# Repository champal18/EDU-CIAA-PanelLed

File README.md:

# EDU-CIAA-PanelLed
Poncho EDU-CIAA

Proyecto de alumnos de ingenieria en computacion de la Universidad Nacional de La Plata.
Desarrollo de poncho para EDU-CIA NXP.
Controlador de panel led + Interfaz de usuario.

Firmware y diseño completo. Se adjunta el informe final para facilitar su comprension.

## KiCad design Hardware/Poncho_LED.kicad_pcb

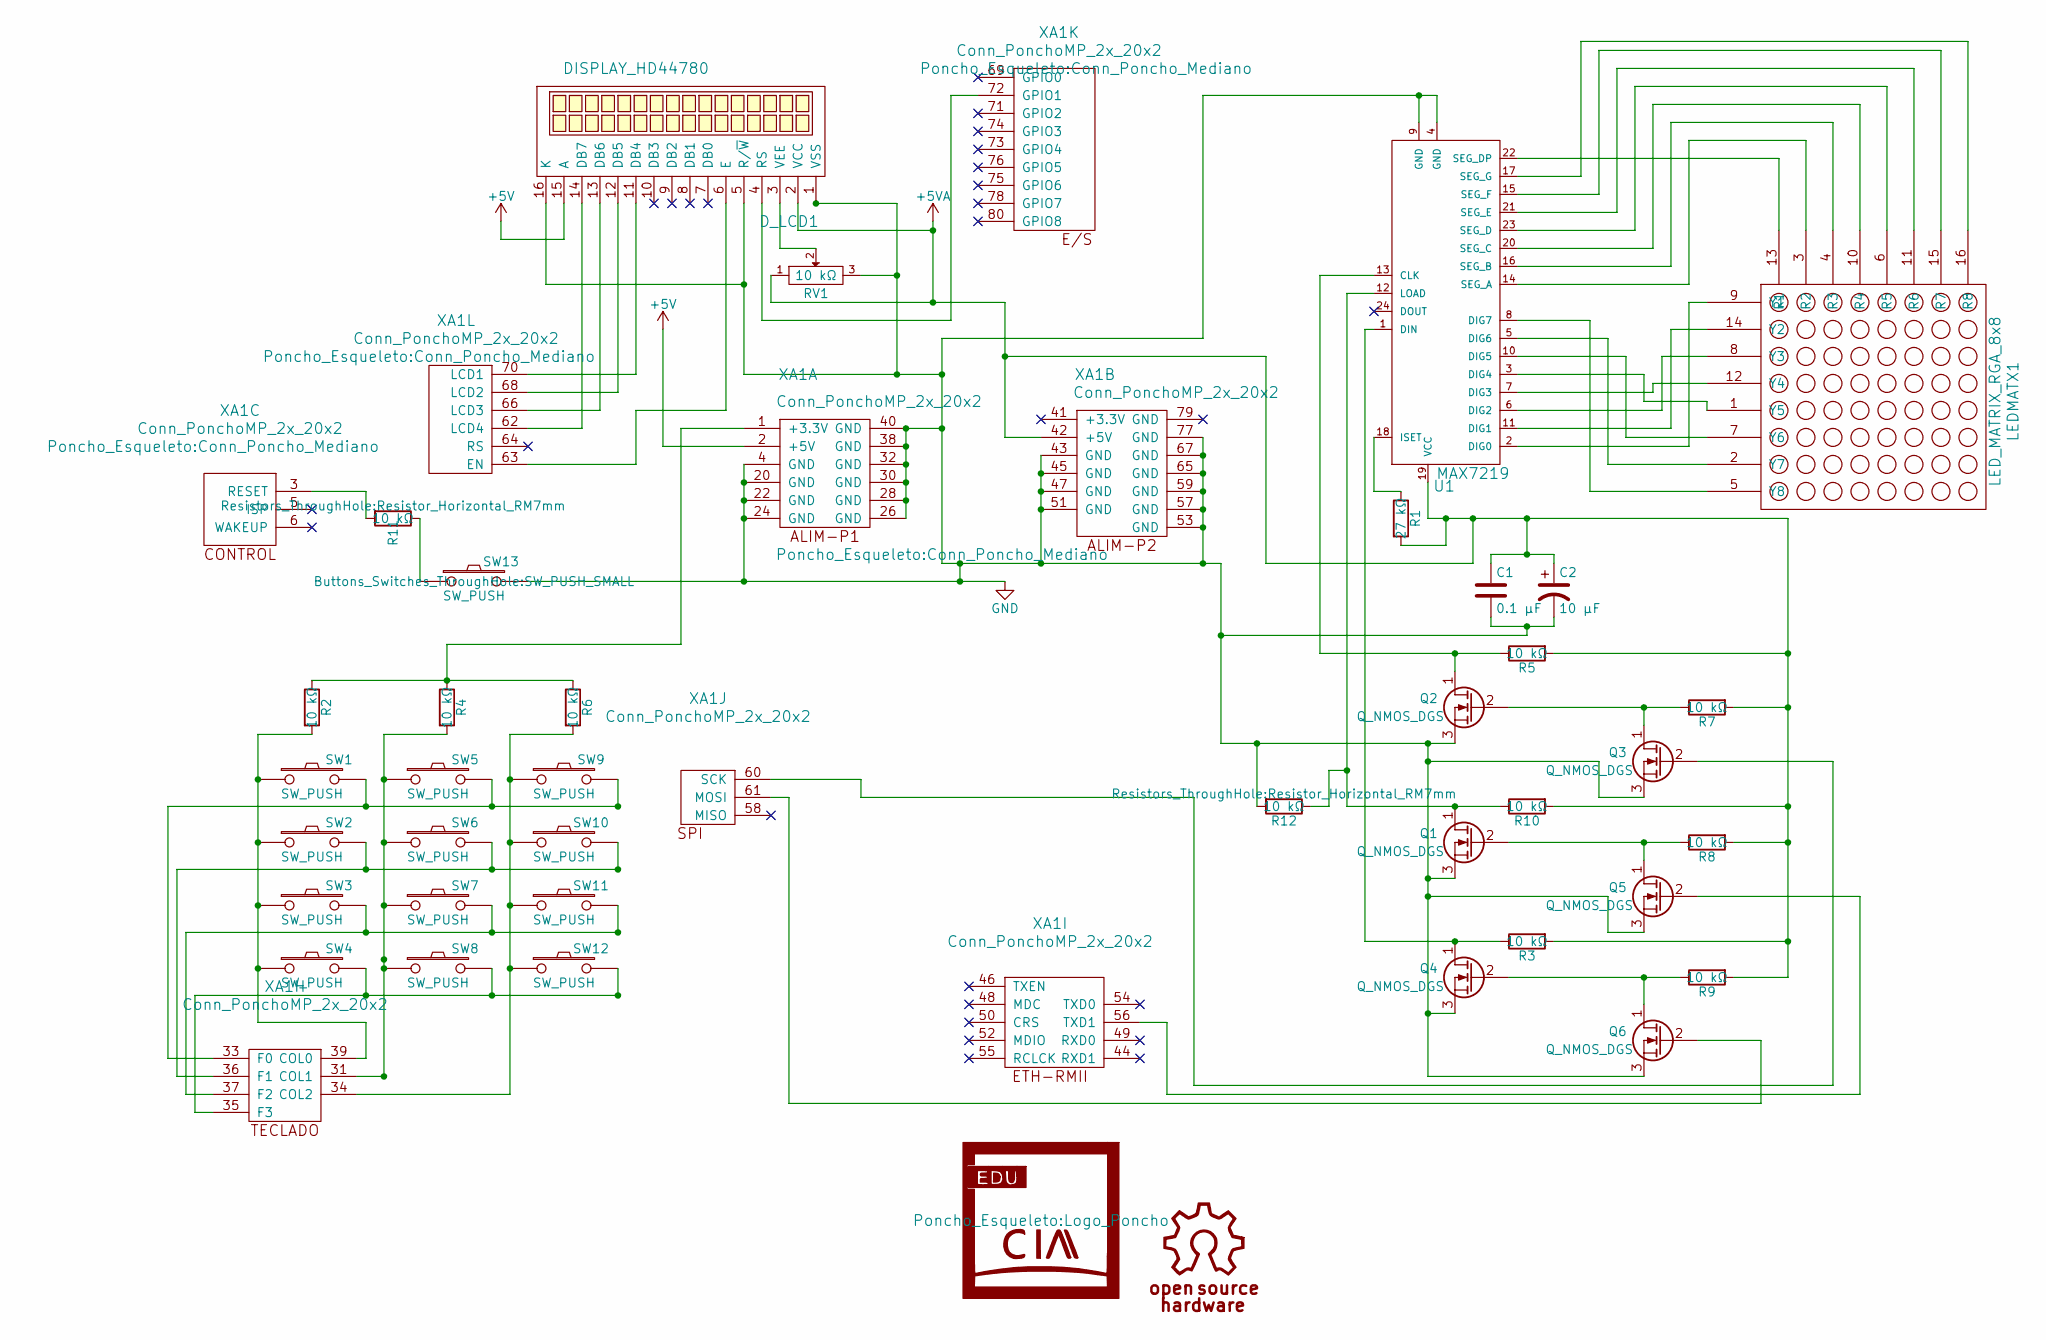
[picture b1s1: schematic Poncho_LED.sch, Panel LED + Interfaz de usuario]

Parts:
C1: 0.1 µF; C_Disc_D3_P2.5
C2: 10 µF; C_Radial_D5_L11_P2.5
D_LCD1: DISPLAY_HD44780; LCD-16x2
LEDMATX1: LED_MATRIX_RGA_8x8; LED_ALE
Q1, Q2, Q3, Q4, Q5, Q6: Q_NMOS_DGS; TO-92_Inline_Narrow_Oval
R1: 27 kΩ; Resistor_Horizontal_RM7mm
R2, R3, R4, R5, R6, R7, R8, R9, R10, R11, R12: 10 kΩ; Resistor_Horizontal_RM7mm
RV1: 10 kΩ; Potentiometer_Bourns_3006P_Angular_ScrewFront
SW1, SW2, SW3, SW4, SW5, SW6, SW7, SW8, SW9, SW10, SW11, SW12, SW13: SW_PUSH; SW_PUSH_SMALL
U1: MAX7219; DIP-24_W7.62mm_LongPads
XA1: Conn_PonchoMP_2x_20x2; Conn_Poncho_Mediano

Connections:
+5V: D_LCD1.15 (A), XA1.2 (+5V)
+5VA: C1.1, C2.1, D_LCD1.2 (VCC), R1.2, R3.2, R5.2, R7.2, R8.2, R9.2, R10.2, RV1.1, U1.19 (VCC), XA1.42 (+5V)
GND: C1.2, C2.2, D_LCD1.1 (VSS), D_LCD1.5 (R/~W), D_LCD1.16 (K), Q1.3 (S), Q2.3 (S), Q3.3 (S), Q4.3 (S), Q5.3 (S), Q6.3 (S), R12.2, RV1.3, SW13.2, U1.4 (GND), U1.9 (GND), XA1.4 (GND), XA1.20 (GND), XA1.22 (GND), XA1.24 (GND), XA1.26 (GND), XA1.28 (GND), XA1.30 (GND), XA1.32 (GND), XA1.38 (GND), XA1.40 (GND), XA1.43 (GND), XA1.45 (GND), XA1.47 (GND), XA1.51 (GND), XA1.53 (GND), XA1.57 (GND), XA1.59 (GND), XA1.65 (GND), XA1.67 (GND), XA1.77 (GND)
unnamed: D_LCD1.3 (VEE), RV1.2
unnamed: D_LCD1.4 (RS), XA1.72 (GPIO1)
unnamed: D_LCD1.6 (E), XA1.63 (EN)
unnamed: D_LCD1.11 (DB4), XA1.70 (LCD1)
unnamed: D_LCD1.12 (DB5), XA1.68 (LCD2)
unnamed: D_LCD1.13 (DB6), XA1.66 (LCD3)
unnamed: D_LCD1.14 (DB7), XA1.62 (LCD4)
unnamed: LEDMATX1.1 (Y5), U1.3 (DIG4)
unnamed: LEDMATX1.2 (Y7), U1.5 (DIG6)
unnamed: LEDMATX1.3 (R2), U1.14 (SEG_A)
unnamed: LEDMATX1.4 (R3), U1.16 (SEG_B)
unnamed: LEDMATX1.5 (Y8), U1.8 (DIG7)
unnamed: LEDMATX1.6 (R5), U1.23 (SEG_D)
unnamed: LEDMATX1.7 (Y6), U1.10 (DIG5)
unnamed: LEDMATX1.8 (Y3), U1.6 (DIG2)
unnamed: LEDMATX1.9 (Y1), U1.2 (DIG0)
unnamed: LEDMATX1.10 (R4), U1.20 (SEG_C)
unnamed: LEDMATX1.11 (R6), U1.21 (SEG_E)
unnamed: LEDMATX1.12 (Y4), U1.7 (DIG3)
unnamed: LEDMATX1.13 (R1), U1.22 (SEG_DP)
unnamed: LEDMATX1.14 (Y2), U1.11 (DIG1)
unnamed: LEDMATX1.15 (R7), U1.15 (SEG_F)
unnamed: LEDMATX1.16 (R8), U1.17 (SEG_G)
unnamed: Q1.1 (D), R10.1, R12.1, U1.12 (LOAD)
unnamed: Q1.2 (G), Q5.1 (D), R8.1
unnamed: Q2.1 (D), R5.1, U1.13 (CLK)
unnamed: Q2.2 (G), Q3.1 (D), R7.1
unnamed: Q3.2 (G), XA1.60 (SCK)
unnamed: Q4.1 (D), R3.1, U1.1 (DIN)
unnamed: Q4.2 (G), Q6.1 (D), R9.1
unnamed: Q5.2 (G), XA1.56 (TXD1)
unnamed: Q6.2 (G), XA1.61 (MOSI)
unnamed: R1.1, U1.18 (ISET)
unnamed: R2.1, R4.1, R6.1, XA1.1 (+3.3V)
unnamed: R2.2, SW1.1, SW2.1, SW3.1, SW4.1, XA1.39 (COL0)
unnamed: R4.2, SW5.1, SW6.1, SW7.1, SW8.1, XA1.31 (COL1)
unnamed: R6.2, SW9.1, SW10.1, SW11.1, SW12.1, XA1.34 (COL2)
unnamed: R11.1, SW13.1
unnamed: R11.2, XA1.3 (RESET)
unnamed: SW1.2, SW5.2, SW9.2, XA1.33 (F0)
unnamed: SW2.2, SW6.2, SW10.2, XA1.36 (F1)
unnamed: SW3.2, SW7.2, SW11.2, XA1.37 (F2)
unnamed: SW4.2, SW8.2, SW12.2, XA1.35 (F3)

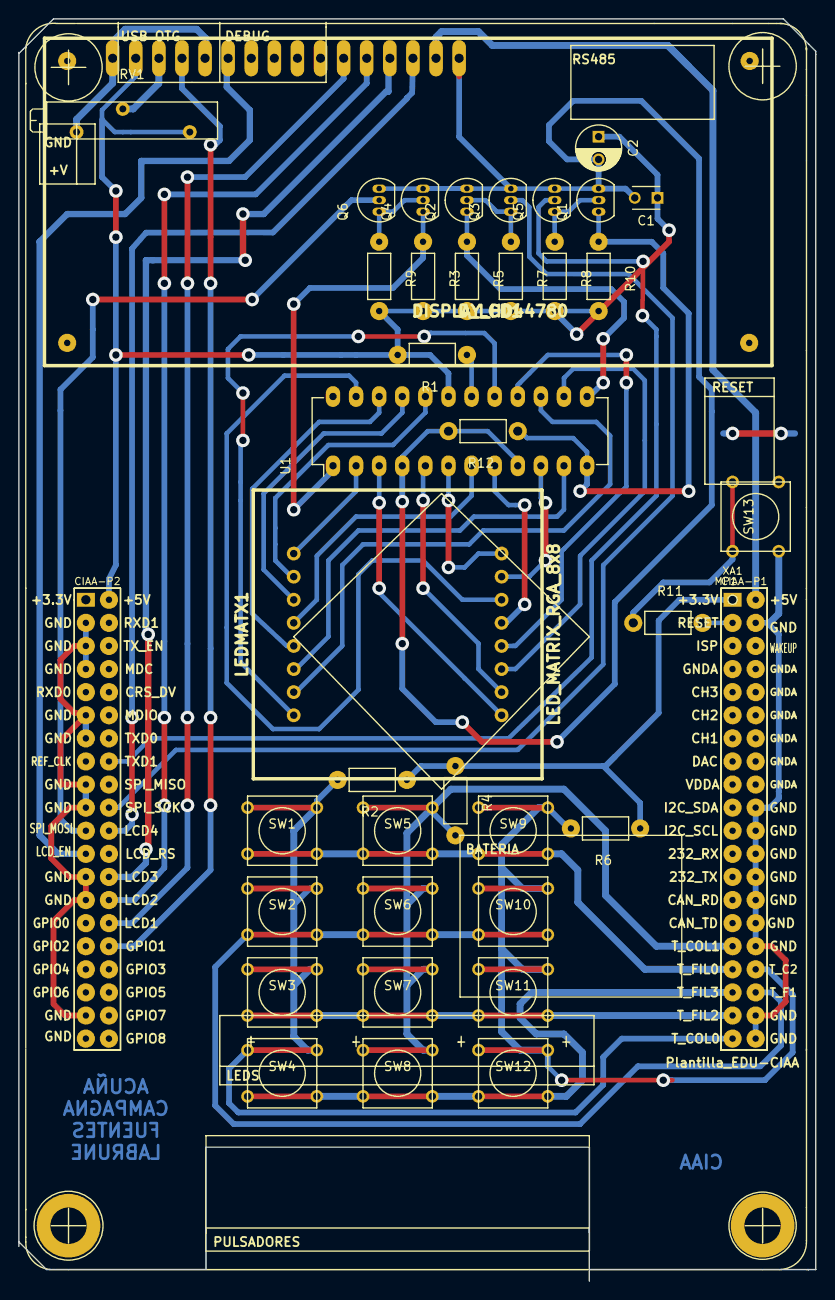
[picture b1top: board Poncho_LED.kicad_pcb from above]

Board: 2 copper layers, 87.6 x 138.8 mm, 39 parts (0 on the bottom side), 46 nets.

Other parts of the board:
MP1: Plantilla_EDU-CIAA

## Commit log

2016-03-28 :circus_tent: Added .gitattributes & .gitignore files
2016-03-28 Firmware
    Poncho:
    Controlador de panel led + Interfaz de usuario
2016-03-28 Extras
    Informe
    Presentación
    Diseño de placa
2016-03-28 Corrección gitignore
